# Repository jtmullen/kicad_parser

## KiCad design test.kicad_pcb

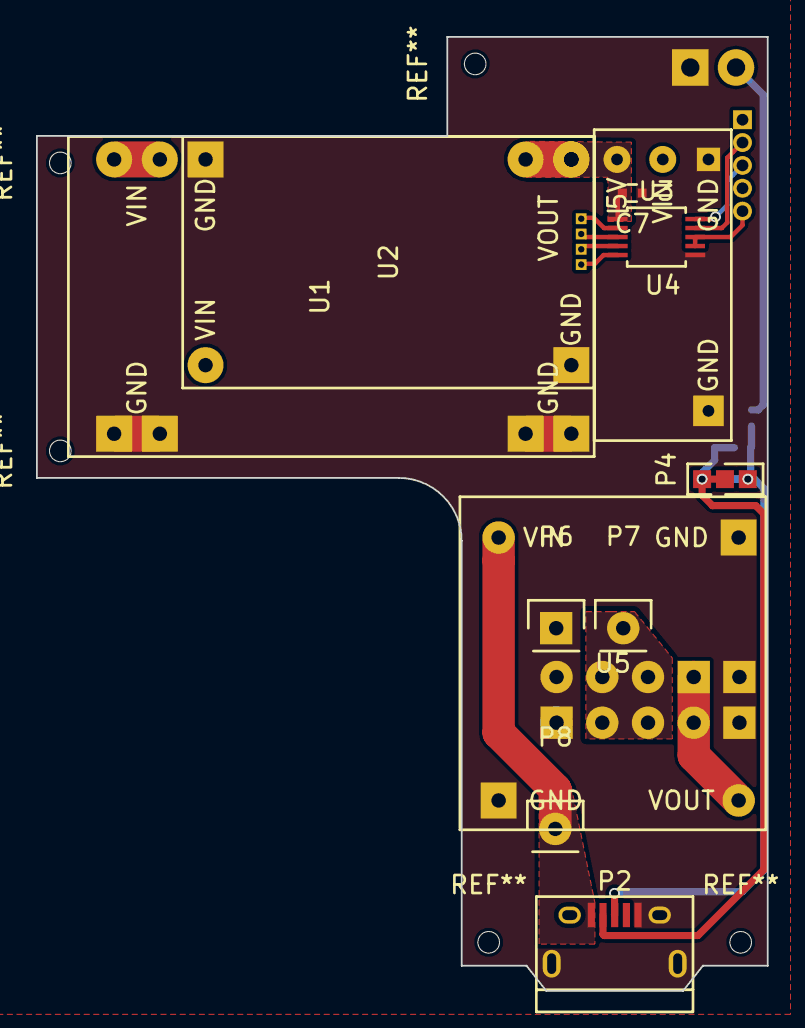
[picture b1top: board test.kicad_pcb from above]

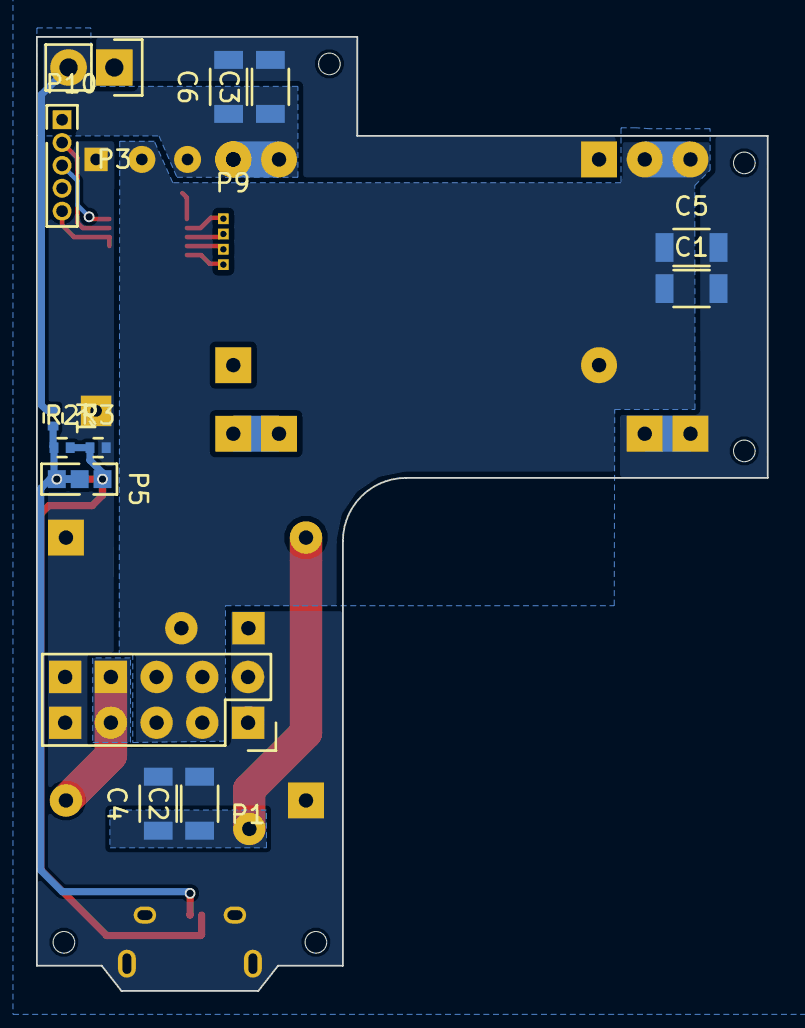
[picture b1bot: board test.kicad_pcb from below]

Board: 2 copper layers, 40.6 x 53.0 mm, 25 parts (14 on the bottom side), 14 nets.

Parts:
C1, C2, C3, C4, C5, C6: 47uF; C_1206
C7: 100nF; C_0402
P1: CONN5; Socket_Strip_Straight_2x05
P2: USB_Micro; USB_Micro-B
P3: CONN_VCC; Socket_Strip_Straight_1x02
P4, P5: CONN_01X03; Pin_Header_Straight_1x03_Pitch1.27mm
P6, P7, P8: CONN_01X01; Pin_Header_Straight_1x01
P9: CONN_01X02; Pin_Header_Straight_1x04_Pitch1.27mm
P10: CONN_01X05; Socket_Strip_Straight_1x05_Pitch1.27mm
R1: 2M; R_0402
R2: 1M; R_0402
R3: 400K; R_0402
U1: TPS61800 module; DCDC_Conv_TPS61088_Boost
U2: G5177 module; DCDC_Conv_G5177-Boost
U3: TMP432; TSSOP-10_3x3mm_Pitch0.5mm
U4: LDO_3V5; LDO_RT9018
U5: TP5000 Charger; DCDC_Charger-TP5000-Bucket

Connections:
/BAT: C1.1, C5.1, P1.3, P1.4, P1.5, P1.6, P7.1, U1.2, U2.2, U4.2
/CHARGE: P1.7, P1.8, U5.3
/CHG_IN: C2.1, C4.1, P2.1, P8.1, U5.2
/D1+: P9.1, U3.2
/D1-: P9.2, U3.3
/D2+: P9.3, U3.4
/D2-: P9.4, U3.5
/SCL1: P10.3, U3.10
/SDA1: P10.2, U3.9
/TMP_INT: P10.5, U3.7, U3.8
/V0.6: P2.2, P4.1, P4.2, P5.1, R2.2, R3.1
/V3.3: P2.3, P4.3, P5.2, P5.3, R1.2, R2.1
GND: C1.2, C2.2, C3.2, C4.2, C5.2, C6.2, C7.1, P1.1, P1.2, P1.9, P1.10, P2.5, P2.6, P3.1, P6.1, R3.2, U1.1, U2.1, U3.6, U4.1, U5.1
VCC: C3.1, C6.1, C7.2, P3.2, R1.1, U1.3, U2.3, U3.1, U4.3

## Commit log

2022-03-08 Kicad SCH
2022-03-08 PCB in v6
